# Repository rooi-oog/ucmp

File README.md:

USB-I2C programmer based on STM32F070 uC
=======================================================

Pinout
------
	PA0	-> SCL
	PA1     -> SDA

There are some additional pins on board currently unused. They are reserved for future.

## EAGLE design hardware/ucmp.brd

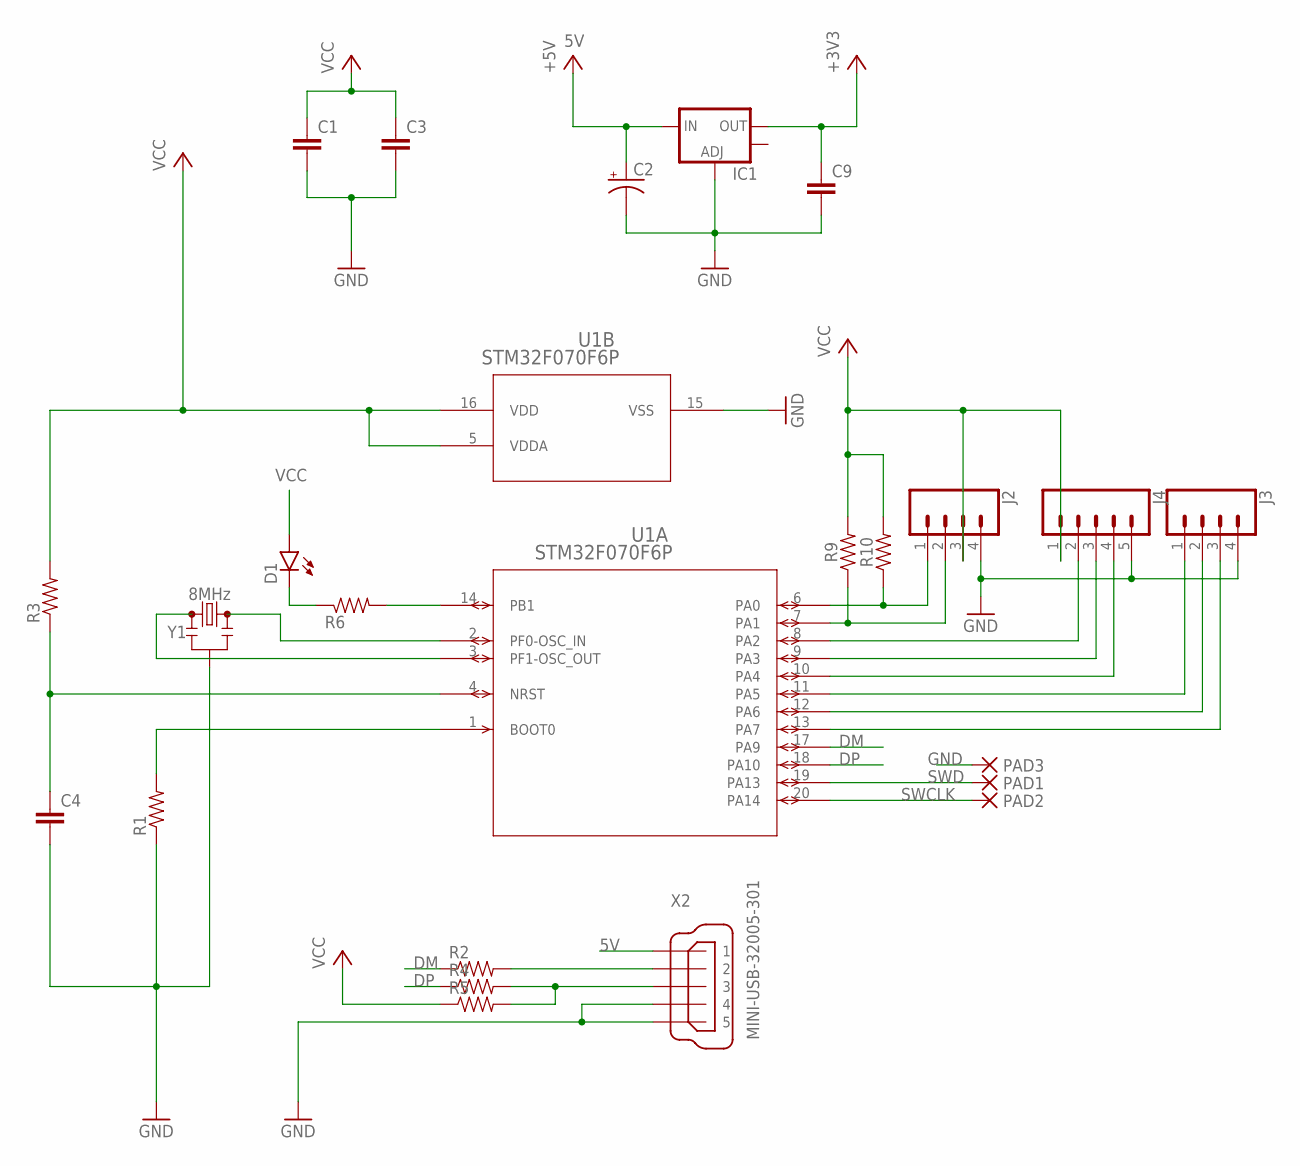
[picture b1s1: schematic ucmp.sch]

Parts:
C1, C3, C4: CAP0805; 0805
C2: CAP_POL3528-KIT; EIA3528-KIT
C9: CAP1206; 1206
D1: LED0603; LED-0603
IC1: V_REG_LM1117SOT223; SOT223
J2, J3: CONN_041.27MM; 1X04_1.27MM
J4: CONN_051.27MM; 1X05_1.27MM
PAD1, PAD2, PAD3: PAD-SMD07R; SMD07R
R1, R2, R3, R4, R5, R6: 4.7OHM-1/10W-5%(0603); 0603-RES
R9, R10: 0805
U1: STM32F070F6P; TSSOP20
X2: MINI-USB-32005-301; 32005-301
Y1: 8MHz; RESONATOR-SMD-3.2X1.3

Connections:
5V: C2.A (+), IC1.3 (IN), X2.1
DM: R2.1, U1.17 (PA9)
DP: R4.1, U1.18 (PA10)
GND: C1.2, C2.C (-), C3.2, C4.2, C9.2, IC1.1 (ADJ), J2.4, J3.4, J4.5, PAD3.PAD, R1.1, U1.15 (VSS), X2.4, X2.5, Y1.2
unnamed: R1.2, U1.1 (BOOT0)
unnamed: C4.1, R3.1, U1.4 (NRST)
unnamed: R6.2, U1.14 (PB1)
unnamed: D1.C, R6.1
unnamed: J2.1, R10.1, U1.6 (PA0)
unnamed: J2.2, R9.1, U1.7 (PA1)
unnamed: J4.2, U1.8 (PA2)
unnamed: J4.3, U1.9 (PA3)
unnamed: J4.4, U1.10 (PA4)
unnamed: R2.2, X2.2
unnamed: J3.1, U1.11 (PA5)
unnamed: R4.2, R5.2, X2.3
unnamed: J3.2, U1.12 (PA6)
unnamed: J3.3, U1.13 (PA7)
unnamed: U1.2 (PF0-OSC_IN), Y1.3
unnamed: U1.3 (PF1-OSC_OUT), Y1.1
SWCLK: PAD2.PAD, U1.20 (PA14)
SWD: PAD1.PAD, U1.19 (PA13)
VCC: C1.1, C3.1, C9.1, D1.A, IC1.2 (OUT), J2.3, J4.1, R3.2, R5.1, R9.2, R10.2, U1.5 (VDDA), U1.16 (VDD)

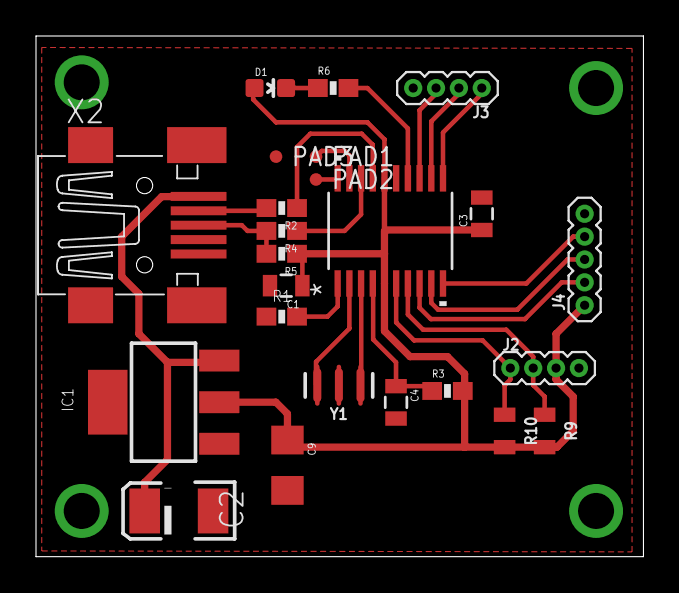
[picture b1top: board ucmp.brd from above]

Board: 2 copper layers, 33.7 x 28.9 mm, 24 parts (0 on the bottom side), 23 nets.

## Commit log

2018-06-18 slightly modify _read func
2018-06-18 slightly modified _read func
2018-06-19 remove some warnings
2018-06-20 Remove errors
2018-06-20 Buffer overlap fix
2018-06-20 Add uart
2018-06-20 Update LICENSE
2018-06-27 SPI improve
2018-06-27 Remove gpio conflicts

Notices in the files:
parts and their libraries:
SparkFun-Capacitors: Licensing: Creative Commons ShareAlike 4.0 International - https://creativecommons.org/licenses/by-sa/4.0
dpads: Copyright (C) 2004, Bob Starr (bobstarr@mindspring.com)
COPYRIGHT: Copyright C 2016 Accelerated Designs. All rights reserved
